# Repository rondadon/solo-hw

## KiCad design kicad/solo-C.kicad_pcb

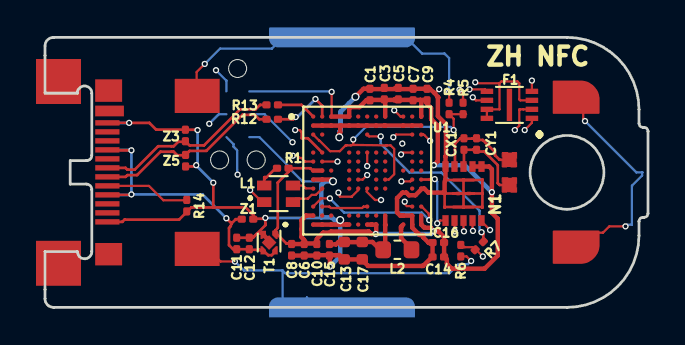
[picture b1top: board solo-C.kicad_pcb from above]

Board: 4 copper layers, 33.5 x 15.0 mm, 38 parts (1 on the bottom side), 34 nets.

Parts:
C1, C3, C5, C6, C7, C8, C9, C10, C11, C12: 4.7u; 0201_C
C13, C17: 10uF; C_0402_1005Metric
C14, C15: 100nF; 0201_C
C16: 47pF; 0201_C
CX1: DNP; 0201_C
CY1: DNP; 0201_C
D1: ARM_DEBUG; TC2030-IDC-NL
F1: GD25Q16CEIGR; FLASH_2x3_USON8
L1: LED_RGBA; RGB_LED_606
L2: 4u7H; L_0603_1608Metric
N1: FM11NC08I; MLPD3X3
P1: USB_C_Plug; USB-C_WURTH
R1: 180R; 0201_R
R4, R6: 10k; 0201_R
R5, R7: 1M; 0201_R
R12, R13: 33R; 0201_R
R14: 5k; 0201_R
T1: TLV742p; Texas_X2SON-4_1x1mm_P0.65mm
TOP1: TOP_C; top-C
U1: LPC55S28JEV98K; BGA98C50P13X13_700X700X97N
Z1, Z3, Z5: ESDZV5-1BF4; 0201_R
caps1: side_buttons

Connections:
+3V3: C1.1, C3.1, C5.1, C6.1, C7.1, C8.1, C9.1, C10.1, C14.1, C16.1, D1.1, N1.1, N1.2, R1.1, T1.1, U1.A3, U1.A5, U1.A9, U1.A13, U1.G1, U1.G2, U1.M1, U1.M13, U1.N7, U1.N8, U1.N13
/5V: C11.1, C12.1, P1.A4, P1.A9, P1.B4, P1.B9, T1.3, T1.4, Z1.1
/CAP1: R4.1, TOP1.5, caps1.1
/CAP2: R6.1, TOP1.6, caps1.2
/CAP3: TOP1.9, caps1.3
/IN_D+: P1.A6, R12.2, Z5.1
/IN_D-: P1.A7, R13.2, Z3.1
/NFC+: CX1.1, CY1.1, N1.4, TOP1.7
/NFC-: CX1.2, CY1.2, N1.3, TOP1.8
/solo/D+: R12.1, U1.A2
/solo/D-: R13.1, U1.A1
/solo/FLASH_CS: F1.1, U1.C12
/solo/FLASH_POWER: F1.3, F1.7, F1.8, U1.E7
/solo/Sheet5DDC9C58/B: L1.1, U1.J1
/solo/Sheet5DDC9C58/CHARGE1: R5.2, R7.2, U1.C7
/solo/Sheet5DDC9C58/G: L1.2, U1.J2
/solo/Sheet5DDC9C58/NFC_GPIO: N1.10, U1.L12
/solo/Sheet5DDC9C58/R: L1.3, U1.H6
/solo/Sheet5DDC9C58/SENSE1: R4.2, R5.1, U1.C1, U1.H9
/solo/Sheet5DDC9C58/SENSE2: R6.2, R7.1, U1.L1, U1.L13
/solo/Sheet5DDC9C58/SENSE3: U1.L2, U1.L7
/solo/Sheet5DDC9C58/SPI_CLK: F1.6, N1.7, U1.C13, U1.H12
/solo/Sheet5DDC9C58/SPI_MISO: F1.2, N1.9, U1.A11, U1.J7
/solo/Sheet5DDC9C58/SPI_MOSI: F1.5, N1.8, U1.E12
/solo/Sheet5DDC9C58/SPI_SS: N1.6, U1.H13
/solo/Sheet5DDC9C58/SWCLK: D1.4, U1.F1
/solo/Sheet5DDC9C58/SWDIO: D1.2, U1.E2
/solo/Sheet5DDC9C58/SWO: D1.6, U1.F2
/solo/nRESET: D1.3, U1.J6
GNDREF: C1.2, C3.2, C5.2, C6.2, C7.2, C8.2, C9.2, C10.2, C11.2, C12.2, C13.2, C14.2, C15.2, C16.2, C17.2, D1.5, F1.4, N1.5, N1.EXP, P1.A1, P1.A12, P1.B1, P1.B12, R14.2, T1.2, T1.5, U1.B1, U1.B2, U1.B3, U1.B5, U1.B6, U1.B7, U1.B8, U1.B9, U1.B11, U1.B12, U1.B13, U1.H1, U1.H2, U1.J13, U1.M11, U1.M12, U1.N1, U1.N2, U1.N3, U1.N5, U1.N12, Z1.2, Z3.2, Z5.2
unnamed: C13.1, C15.1, C17.1, L2.2, U1.M9, U1.N9
unnamed: L1.4, R1.2
unnamed: L2.1, U1.N11
unnamed: P1.A5, R14.1

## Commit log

2020-01-14 new nfc chip layout
